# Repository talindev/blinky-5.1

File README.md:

<h1 align="center">Blinky 5.1</h1>

-success?style=flat-square)

This is an implementation of Contextual Electronics course "Getting to Blinky 5.0", this is my first fab-ready start-to-finish PCB. I added my touch with a 500 kΩ potentiometer, to adjust the simetrical speed of the charge-discharge capacitor cycle.

---

## 1. Design Overview & Hardware Modifications

While the baseline *Getting to Blinky 5.0* uses a fixed timing 470 kΩ resistor (R<sub>2</sub>), this revision replaces R<sub>2</sub> with a **SMD 500 kΩ linear trimmer potentiometer (`RV1`, Bourns 3314G)**. This allows continuous hardware adjustment of the oscillation frequency across three orders of magnitude (1.44 Hz to 1.44 kHz) without firmware or external instrumentation.

### fun facts :)
- **100% Top-Side SMD Component Placement:** Keeps the bottom layer (`B.Cu`) free of through-hole leads, eliminating mechanical interference with the rear-mounted CR2032 battery clip (`BT1`) and preserving ground plane continuity.
- **Split Power/Ground Plane Strategy:** Dedicated `+3V` (`VDD`) copper pour on `F.Cu` paired with a solid `GND` reference plane on `B.Cu`.
- **Hand-Soldering Optimization:** Uses IPC-compliant `_HandSolder` extended pads for all `0805` passives, 4-spoke thermal reliefs on high-mass copper connections, and via-in-pad avoidance (*dog-bone* trace offsets) to prevent solder wicking.

---

## 2. Circuit Architecture & Theory of Operation

The circuit operates as a classic **CMOS 555 Astable Multivibrator** powered by a nominal 3.0 V lithium coin cell (`BT1`).

### Functional Block Breakdown
1. **Internal Voltage Divider (3 × 5 kΩ):** Establishes ratiometric switching thresholds at 1/3 V<sub>DD</sub> (1.0 V) and 2/3 V<sub>DD</sub> (2.0 V). Because capacitor charging follows an exponential curve proportional to V<sub>DD</sub>, supply voltage variations cancel out, keeping oscillation frequency stable as the CR2032 discharges.
2. **Charge Phase (`OUT` = HIGH, `DISCHARGE` = High-Z):**
   * When V<sub>C1</sub> < 1/3 V<sub>DD</sub>, the lower comparator sets the internal SR flip-flop.
   * `U1` Pin 3 (`OUT`) drives `+3V` through current-limiting resistor `R3` (1 kΩ), forward-biasing `D1`.
   * Simultaneously, `C1` (1 µF) charges from `VDD` through `R1` (1 kΩ) in series with `RV1` (0–500 kΩ).
3. **Discharge Phase (`OUT` = LOW, `DISCHARGE` = GND):**
   * Once V<sub>C1</sub> reaches 2/3 V<sub>DD</sub>, the upper comparator resets the flip-flop.
   * `U1` Pin 3 drops to 0 V (turning off `D1`), and Pin 7 (`DISCHARGE`) saturates an internal open-drain MOSFET to `GND`.
   * `C1` discharges exclusively through `RV1` into Pin 7 until V<sub>C1</sub> drops back to 1/3 V<sub>DD</sub>, restarting the cycle.
4. **Fail-Safe Rheostat & Short-Circuit Protection:**
   * `RV1` Pin 3 is shorted directly to Pin 2 (*wiper*). If the mechanical wiper momentarily loses contact during adjustment, the resistance defaults to the full 500 kΩ track rather than creating an open circuit.
   * `R1` (1 kΩ) remains fixed in series with `VDD`, limiting maximum sink current into Pin 7 to 3.0 mA even when `RV1` is dialed to 0 Ω.

---

## 3. Mathematical Modeling & Timing Envelope

The charge (t<sub>HIGH</sub>) and discharge (t<sub>LOW</sub>) intervals are governed by the RC time constant τ = R · C between the 1/3 V<sub>DD</sub> and 2/3 V<sub>DD</sub> thresholds (ln(2) ≈ 0.693):

$$
t_{\mathrm{HIGH}} = \ln(2) \cdot (R_1 + R_{V1}) \cdot C_1
$$

$$
t_{\mathrm{LOW}} = \ln(2) \cdot R_{V1} \cdot C_1
$$

$$
f = \frac{1}{t_{\mathrm{HIGH}} + t_{\mathrm{LOW}}} = \frac{1}{\ln(2) \cdot (R_1 + 2R_{V1}) \cdot C_1}
$$

$$
\mathrm{Duty\ Cycle\ (\%)} = \frac{R_1 + R_{V1}}{R_1 + 2R_{V1}} \times 100\%
$$

### Operating Sweep (R<sub>1</sub> = 1 kΩ, C<sub>1</sub> = 1 µF)

| `RV1` Position | Effective R<sub>V1</sub> | t<sub>HIGH</sub> | t<sub>LOW</sub> | Frequency (f) | Duty Cycle | Visual Behavior |
| :--- | :--- | :--- | :--- | :--- | :--- | :--- |
| **0% (CCW Min)** | ~0 Ω | 0.69 ms | ~0.02 ms* | **~1.44 kHz** | ~97.2% | Appears continuously lit (above flicker fusion threshold) |
| **50% (Mid-Span)** | 250 kΩ | 173.9 ms | 173.3 ms | **2.88 Hz** | 50.1% | Fast, symmetric rhythmic blink |
| **100% (CW Max)** | 500 kΩ | 347.2 ms | 346.5 ms | **1.44 Hz** | 50.05% | Slow, distinct pulse (~1.4 blinks/sec) |

*\*Bounded by the internal `DISCHARGE` MOSFET on-resistance (R<sub>DS(on)</sub> ≈ 20–30 Ω).*

---

## 4. PCB Stackup, Copper Pours & Routing Architecture

### 2-Layer Standard FR-4 Stackup
| Layer | Name | Type | Copper Weight | Role & Plane Assignment |
| :--- | :--- | :--- | :--- | :--- |
| **Top** | `F.Cu` | Signal / Power | 1 oz (35 µm) | Component mounting, signal routing (`DIS`, `THR`, `OUT`), and **`VDD` (+3V) copper pour** |
| **Core** | Dielectric | FR-4 (ε<sub>r</sub> ≈ 4.4) | — | 1.6 mm (63 mil) mechanical substrate |
| **Bottom** | `B.Cu` | Ground / Power | 1 oz (35 µm) | Battery clip `BT1`, `VDD` input pads, and continuous **`GND` (0V) reference plane** |

### Layout & Routing Decisions
- **Via Architecture (5 Total Vias):**
  * **2 Power Stitching Vias:** Route `+3V` from the left and right `BT1` positive pads on `B.Cu` up to the `VDD` copper pour on `F.Cu`.
  * **3 Ground Return Vias:** Connect the ground pads of `U1` (Pin 1), `C1` (Pin 2), and `D1` (Pin 1) directly into the solid `B.Cu` `GND` plane.
- **Anti-Wicking Dog-Bones:** Every via is offset from its parent SMD pad via a short trace segment rather than placed inside the pad, preventing molten solder from wicking down the barrel during manual reflow/iron assembly.
- **Thermal Reliefs:** All zone connections (`VDD` on `F.Cu` and `GND` on `B.Cu`, including the large central `BT1` ground pad) use **4-spoke thermal reliefs** to prevent heat sinking into the copper planes during hand soldering.
- **45° Routing Geometry:** All signal traces (`DIS`, `THR`, `OUT`) are routed exclusively on `F.Cu` using 45° corners and generous clearance around the `SOIC-8` gull-wing leads.

---

## 5. Signal Integrity (SI), Impedance & Power Integrity (PI) Analysis

### Microstrip Characteristic Impedance & Transmission Line Regime
Assuming a standard 1.6 mm FR-4 core (ε<sub>r</sub> = 4.4), 1 oz copper (T = 0.035 mm), and standard signal trace width W = 0.25 mm (9.84 mils) referenced over the continuous `B.Cu` `GND` plane:

- **Characteristic Impedance (Z<sub>0</sub>):**
  * **Hammerstad–Jensen Microstrip Model:** Z<sub>0</sub> = **131.0 Ω** (ε<sub>eff</sub> = 2.90)
  * **IPC-2141 Approximation:** Z<sub>0</sub> = **133.8 Ω**
- **Propagation Delay (t<sub>pd</sub>):**

$$
t_{pd} = \frac{\sqrt{\varepsilon_{\mathrm{eff}}}}{c} \approx 5.68\ \mathrm{ps/mm}
$$

- **Critical Length & Lumped-Element Verification:**
  For a CMOS `7555` output transition time of t<sub>r</sub> ≈ 100 ns (signal bandwidth BW ≈ 0.35 / t<sub>r</sub> = 3.5 MHz), the critical transmission-line length threshold (l<sub>crit</sub> = t<sub>r</sub> / (6 · t<sub>pd</sub>)) is **2.93 m**. Since the longest physical trace on this PCB is **< 15 mm** (0.5% of l<sub>crit</sub>), reflections are negligible and controlled-impedance termination is unnecessary.

### Power Budget, Ampacity & Battery Runtime
- **Trace Ampacity (IPC-2221):** A 0.25 mm external 1 oz copper trace supports ~800 mA for a ΔT = 10 °C rise—providing a **>260× current margin** over the circuit's 3.0 mA worst-case branch current.
- **Current Consumption & CR2032 Runtime (~220 mAh capacity):**
  * Quiescent IC current (I<sub>Q</sub>): ~60 µA
  * LED drive current (V<sub>DD</sub> = 3.0 V, V<sub>F</sub> ≈ 1.9 V, R<sub>3</sub> = 1 kΩ): I<sub>LED</sub> = (3.0 − 1.9) / 1000 = 1.1 mA (active during `HIGH`)
  * Discharge sink current through `R1` (1 kΩ): I<sub>R1</sub> = 3.0 / 1000 = 3.0 mA (active during `LOW`)
  * Average current at 50% duty cycle: I<sub>avg</sub> ≈ 0.06 + 0.5(1.1) + 0.5(3.0) = **2.11 mA**
  * **Estimated Continuous Runtime:** 220 mAh / 2.11 mA ≈ **104 hours** (~4.3 days continuous operation).

---

## 6. Bill of Materials (BOM) & Footprint Mapping

| Ref | Value | Description | Package | KiCad Footprint Assignment | Layer |
| :--- | :--- | :--- | :--- | :--- | :--- |
| **`U1`** | `7555` | CMOS Low-Power Timer (LMC555 / TLC555) | SOIC-8 | `Package_SO:SOIC-8_3.9x4.9mm_P1.27mm` | `F.Cu` |
| **`RV1`** | `500K` | Linear SMD Trimmer Potentiometer (1-Turn) | 4.5×4.5 mm | `Potentiometer_SMD:Potentiometer_Bourns_3314G_Vertical` | `F.Cu` |
| **`R1`** | `1K` | Thick-Film Chip Resistor (1%, 1/8 W) | 0805 | `Resistor_SMD:R_0805_2012Metric_Pad1.20x1.40mm_HandSolder` | `F.Cu` |
| **`R3`** | `1K` | Thick-Film Chip Resistor (1%, 1/8 W) | 0805 | `Resistor_SMD:R_0805_2012Metric_Pad1.20x1.40mm_HandSolder` | `F.Cu` |
| **`C1`** | `1U` | MLCC Ceramic Capacitor (16 V, X7R/X5R) | 0805 | `Capacitor_SMD:C_0805_2012Metric_Pad1.18x1.45mm_HandSolder` | `F.Cu` |
| **`D1`** | `LED` | Indicator LED (Red/Green/Amber, V<sub>F</sub> ≈ 1.9 V) | 0805 | `LED_SMD:LED_0805_2012Metric_Pad1.15x1.40mm_HandSolder` | `F.Cu` |
| **`BT1`** | `CR2032` | 3V Coin-Cell Battery Retainer Clip | SMD | `getting_to_blinky:S8211-46R` | `B.Cu` |

---

## 7. DFM Verification & Hardware Bring-Up Procedure

### Pre-Fabrication Checklist
- [x] **ERC (Electrical Rules Checker):** Zero errors/warnings (`PWR_FLAG` assigned on `VDD` and `GND`; Pin 5 `CTRL` flagged `No-Connect`).
- [x] **DRC (Design Rules Checker):** Zero clearance violations, zero unrouted nets, and silkscreen text isolated from exposed solder mask openings.
- [x] **Gerber Inspection:** Verified `F.Cu`, `B.Cu`, `F.Mask`, `B.Mask`, `F.Silkscreen`, `B.Silkscreen`, `Edge.Cuts`, and Excellon drill files.

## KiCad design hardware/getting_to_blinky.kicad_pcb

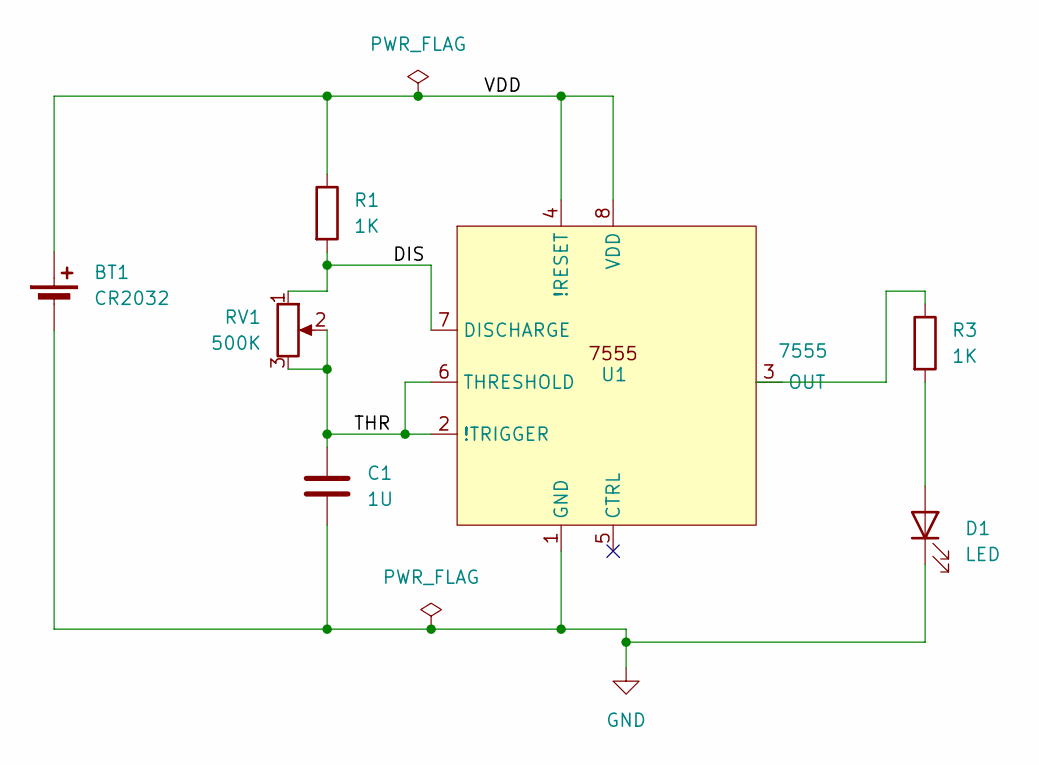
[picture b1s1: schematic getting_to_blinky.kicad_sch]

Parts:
BT1: CR2032; S8211-46R
C1: 1U; C_0805_2012Metric_Pad1.18x1.45mm_HandSolder
D1: LED; LED_0805_2012Metric_Pad1.15x1.40mm_HandSolder
R1, R3: 1K; R_0805_2012Metric_Pad1.20x1.40mm_HandSolder
RV1: 500K; Potentiometer_Bourns_3314G_Vertical
U1: 7555; SOIC-8_3.9x4.9mm_P1.27mm

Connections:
/DIS: R1.2, RV1.1, U1.7 (DISCHARGE)
/THR: C1.1, RV1.2, RV1.3, U1.2 (!TRIGGER), U1.6 (THRESHOLD)
/VDD: BT1.1 (+), R1.1, U1.4 (!RESET), U1.8 (VDD)
GND: BT1.2 (-), C1.2, D1.1 (K), U1.1 (GND)
unnamed: D1.2 (A), R3.2
unnamed: R3.1, U1.3 (OUT)

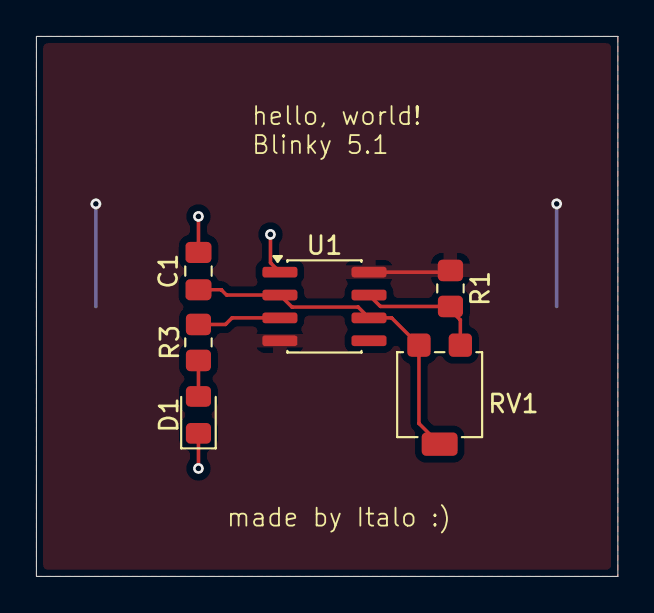
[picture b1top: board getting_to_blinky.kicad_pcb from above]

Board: 2 copper layers, 32.3 x 30.0 mm, 7 parts (1 on the bottom side), 6 nets.

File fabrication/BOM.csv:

"Id";"Designador";"Footprint";"Quantidade";"Designação";"Fornecedor e referência";
1;"BT1";"S8211-46R";1;"CR2032";;;
2;"C1";"C_0805_2012Metric_Pad1.18x1.45mm_HandSolder";1;"1U";;;
3;"D1";"LED_0805_2012Metric_Pad1.15x1.40mm_HandSolder";1;"LED";;;
4;"R1, R3";"R_0805_2012Metric_Pad1.20x1.40mm_HandSolder";2;"1K";;;
5;"RV1";"Potentiometer_Bourns_3314G_Vertical";1;"500K";;;
6;"U1";"SOIC-8_3.9x4.9mm_P1.27mm";1;"7555";;;
